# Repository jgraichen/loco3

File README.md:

# loco3

LocoNet distribution box with power and activity indicator

<p>
  <a href="images/render.png"><a>
  <a href="images/preview.jpeg"><a>
</p>

## License

[CC-BY-SA 4.0](http://creativecommons.org/licenses/by-sa/4.0)

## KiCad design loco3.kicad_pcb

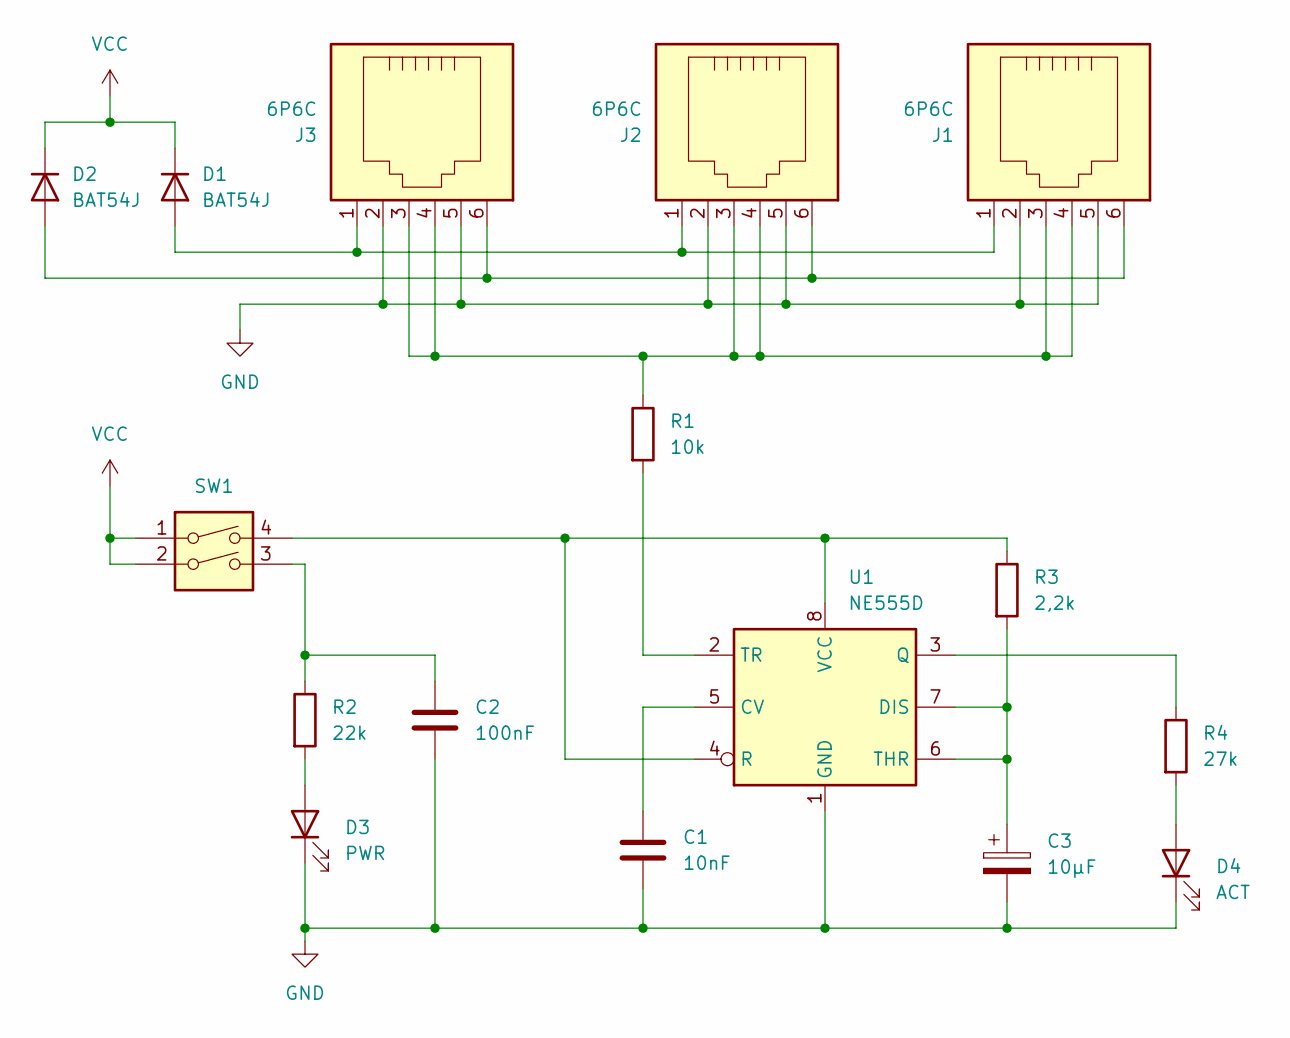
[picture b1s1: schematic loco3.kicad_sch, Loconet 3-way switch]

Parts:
C1: 10nF; C_0603_1608Metric; LCSC C57112
C2: 100nF; C_0603_1608Metric; LCSC C14663
C3: 10µF; C_0805_2012Metric; LCSC C15850
D1, D2: BAT54J; D_SOD-323_HandSoldering; LCSC C191023
D3: PWR; LED_0603_1608Metric; LCSC C2286
D4: ACT; LED_0603_1608Metric; LCSC C2297
J1, J3: 6P6C; A-2004-1-4-LP-N-R_ASSMANN_A-2004-1-4-LP-N-R
J2: 6P6C; A-2014-1-4-N-T-R_ASSMANN_A-2014-1-4-N-T-R
R1: 10k; R_0603_1608Metric; LCSC C25804
R2: 22k; R_0603_1608Metric; LCSC C31850
R3: 2,2k; R_0603_1608Metric; LCSC C4190
R4: 27k; R_0603_1608Metric; LCSC C22967
SW1: SW_DIP_x02; SW_DIP_SPSTx02_Slide_9.78x7.26mm_W7.62mm_P2.54mm; LCSC C319043
U1: NE555D; SOIC-8_3.9x4.9mm_P1.27mm; LCSC C7593

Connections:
GND: C1.2, C2.2, C3.2, D3.1 (K), D4.1 (K), J1.2, J1.5, J2.2, J2.5, J3.2, J3.5, U1.1 (GND)
unnamed: C2.1, R2.1, SW1.3
unnamed: D1.2 (A), J1.1, J2.1, J3.1
unnamed: D2.2 (A), J1.6, J2.6, J3.6
unnamed: D3.2 (A), R2.2
unnamed: D4.2 (A), R4.2
unnamed: J1.3, J1.4, J2.3, J2.4, J3.3, J3.4, R1.1
unnamed: C1.1, U1.5 (CV)
unnamed: C3.1, R3.2, U1.6 (THR), U1.7 (DIS)
unnamed: R4.1, U1.3 (Q)
unnamed: R3.1, SW1.4, U1.4 (R), U1.8 (VCC)
unnamed: R1.2, U1.2 (TR)
VCC: D1.1 (K), D2.1 (K), SW1.1, SW1.2

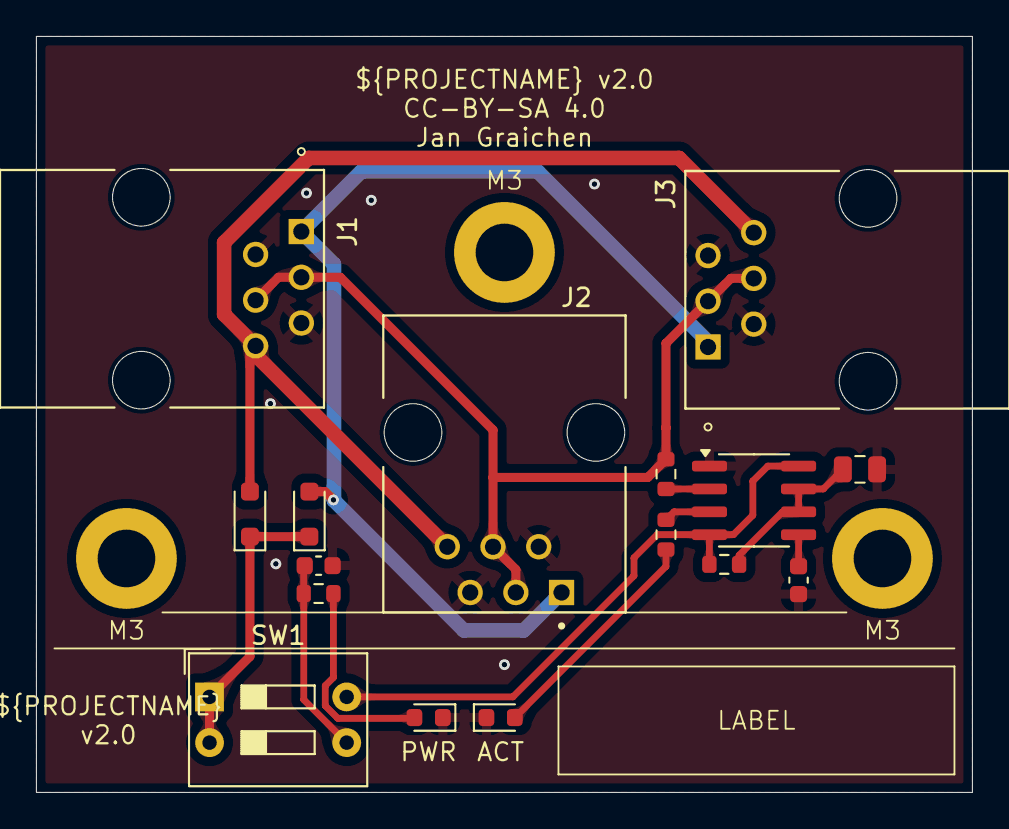
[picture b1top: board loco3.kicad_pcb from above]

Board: 2 copper layers, 52.0 x 42.0 mm, 16 parts (0 on the bottom side), 13 nets.

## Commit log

2024-04-13 Draft
2024-04-13 Update WRL export for MCAD
2024-04-14 feat: Switch to disable LEDs
2024-05-01 Add renovate.json
2024-05-06 feat: Change LED resistors to decrease brightness
2025-04-05 chore: Resize both preview images to same aspect ratio
2025-04-05 Update README
    Equal sized preview images

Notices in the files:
loco3.kicad_sch:
CC-BY-SA 4.0 - Jan Graichen
